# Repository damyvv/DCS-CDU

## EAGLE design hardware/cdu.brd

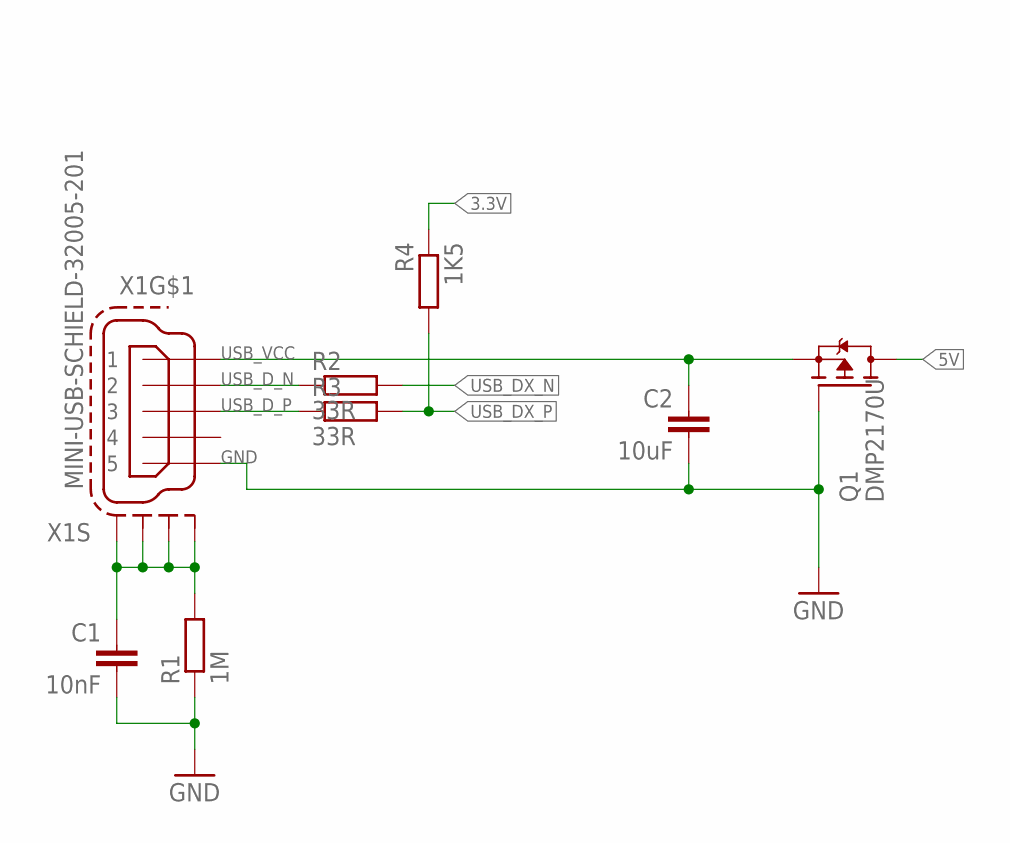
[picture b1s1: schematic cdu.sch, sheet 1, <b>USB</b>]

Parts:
C1: 10nF; C0603
C2: 10uF; C0805K
Q1: DMP2170U; SOT23
R1: 1M; R0603
R2, R3: 33R; R0603
R4: 1K5; R0603
X1: MINI-USB-SCHIELD-32005-201; 32005-201

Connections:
3.3V: R4.1; also elsewhere on the board
5V: Q1.3 (D); also elsewhere on the board
GND: C1.2, C2.2, Q1.1 (G), R1.1, X1.5; also elsewhere on the board
unnamed: C1.1, R1.2, X1.M1 (S1), X1.M2 (S2), X1.M3 (S3), X1.M4 (S4)
USB_DX_N: R2.2; also elsewhere on the board
USB_DX_P: R3.2, R4.2; also elsewhere on the board
USB_D_N: R2.1, X1.2
USB_D_P: R3.1, X1.3
USB_VCC: C2.1, Q1.2 (S), X1.1

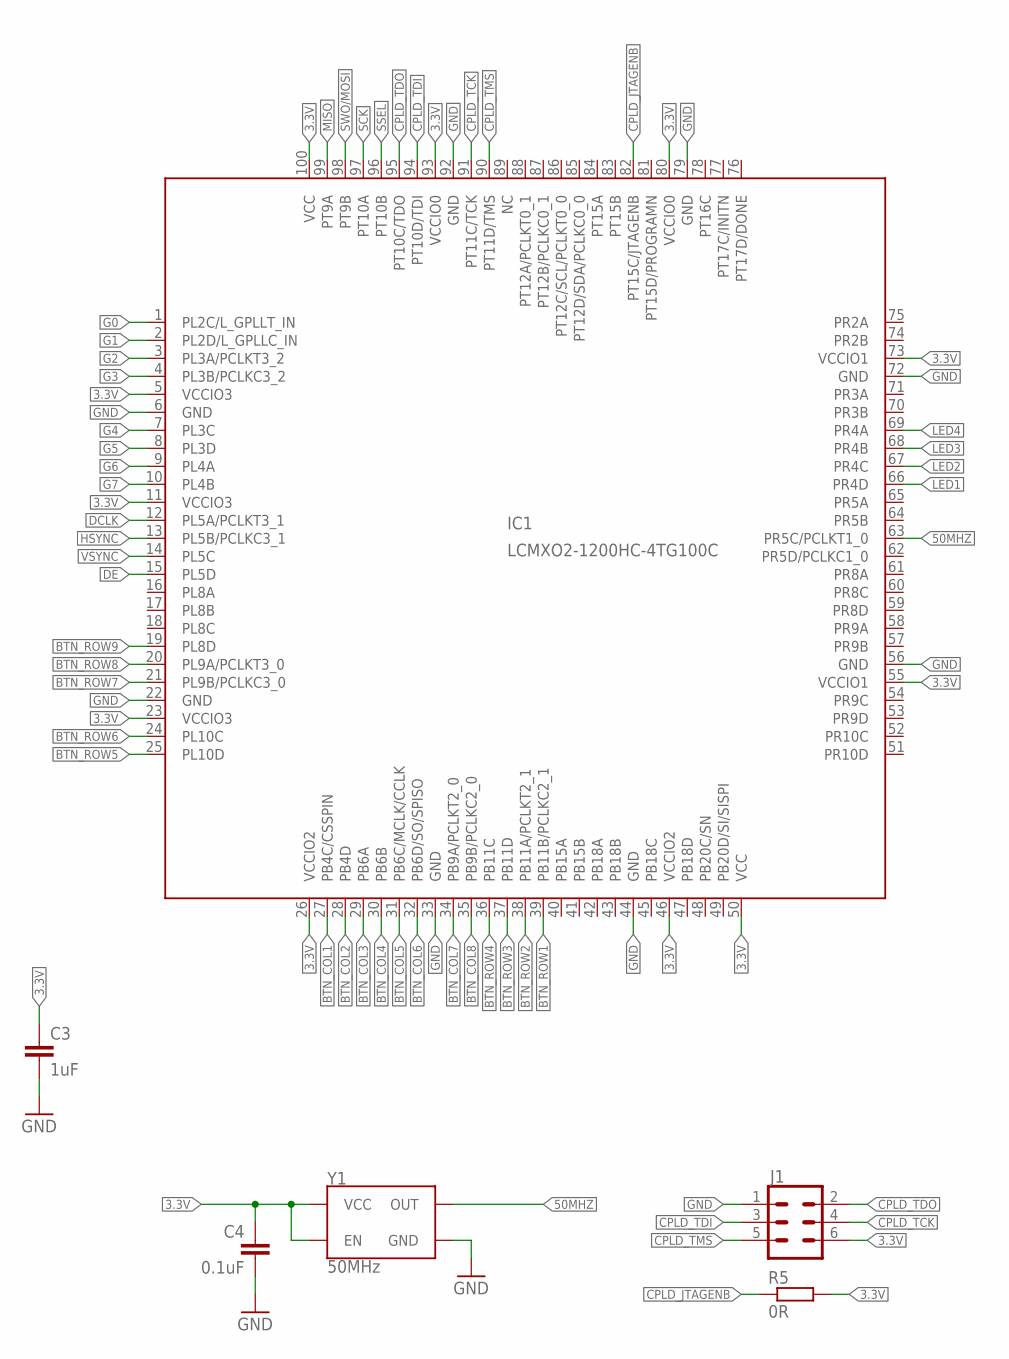
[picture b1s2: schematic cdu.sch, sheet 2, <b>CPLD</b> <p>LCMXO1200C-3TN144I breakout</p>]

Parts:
C3: 1uF; C0603
C4: 0.1uF; C0603
IC1: LCMXO2-1200HC-4TG100C; TQFP100
J1: CONN_03X2FEMALE_SMD; 2X3_SMD
R5: 0R; R0603
Y1: 50MHz; CFPS-73

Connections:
3.3V: C3.1, C4.1, IC1.5 (VCCIO3), IC1.11 (VCCIO3), IC1.23 (VCCIO3), IC1.26 (VCCIO2), IC1.46 (VCCIO2), IC1.50 (VCC), IC1.55 (VCCIO1), IC1.73 (VCCIO1), IC1.80 (VCCIO0), IC1.93 (VCCIO0), IC1.100 (VCC), J1.6, R5.2, Y1.1 (EN), Y1.4 (VCC); also elsewhere on the board
50MHZ: IC1.63 (PR5C/PCLKT1_0), Y1.3 (OUT)
BTN_COL1: IC1.27 (PB4C/CSSPIN); also elsewhere on the board
BTN_COL2: IC1.28 (PB4D); also elsewhere on the board
BTN_COL3: IC1.29 (PB6A); also elsewhere on the board
BTN_COL4: IC1.30 (PB6B); also elsewhere on the board
BTN_COL5: IC1.31 (PB6C/MCLK/CCLK); also elsewhere on the board
BTN_COL6: IC1.32 (PB6D/SO/SPISO); also elsewhere on the board
BTN_COL7: IC1.34 (PB9A/PCLKT2_0); also elsewhere on the board
BTN_COL8: IC1.35 (PB9B/PCLKC2_0); also elsewhere on the board
BTN_ROW1: IC1.39 (PB11B/PCLKC2_1); also elsewhere on the board
BTN_ROW2: IC1.38 (PB11A/PCLKT2_1); also elsewhere on the board
BTN_ROW3: IC1.37 (PB11D); also elsewhere on the board
BTN_ROW4: IC1.36 (PB11C); also elsewhere on the board
BTN_ROW5: IC1.25 (PL10D); also elsewhere on the board
BTN_ROW6: IC1.24 (PL10C); also elsewhere on the board
BTN_ROW7: IC1.21 (PL9B/PCLKC3_0); also elsewhere on the board
BTN_ROW8: IC1.20 (PL9A/PCLKT3_0); also elsewhere on the board
BTN_ROW9: IC1.19 (PL8D); also elsewhere on the board
CPLD_JTAGENB: IC1.82 (PT15C/JTAGENB), R5.1
CPLD_TCK: IC1.91 (PT11C/TCK), J1.4
CPLD_TDI: IC1.94 (PT10D/TDI), J1.3
CPLD_TDO: IC1.95 (PT10C/TDO), J1.2
CPLD_TMS: IC1.90 (PT11D/TMS), J1.5
DCLK: IC1.12 (PL5A/PCLKT3_1); also elsewhere on the board
DE: IC1.15 (PL5D); also elsewhere on the board
G0: IC1.1 (PL2C/L_GPLLT_IN); also elsewhere on the board
G1: IC1.2 (PL2D/L_GPLLC_IN); also elsewhere on the board
G2: IC1.3 (PL3A/PCLKT3_2); also elsewhere on the board
G3: IC1.4 (PL3B/PCLKC3_2); also elsewhere on the board
G4: IC1.7 (PL3C); also elsewhere on the board
G5: IC1.8 (PL3D); also elsewhere on the board
G6: IC1.9 (PL4A); also elsewhere on the board
G7: IC1.10 (PL4B); also elsewhere on the board
GND: C3.2, C4.2, IC1.6 (GND), IC1.22 (GND), IC1.33 (GND), IC1.44 (GND), IC1.56 (GND), IC1.72 (GND), IC1.79 (GND), IC1.92 (GND), J1.1, Y1.2 (GND); also elsewhere on the board
HSYNC: IC1.13 (PL5B/PCLKC3_1); also elsewhere on the board
LED1: IC1.66 (PR4D); also elsewhere on the board
LED2: IC1.67 (PR4C); also elsewhere on the board
LED3: IC1.68 (PR4B); also elsewhere on the board
LED4: IC1.69 (PR4A); also elsewhere on the board
MISO: IC1.99 (PT9A); also elsewhere on the board
SCK: IC1.97 (PT10A); also elsewhere on the board
SSEL: IC1.96 (PT10B); also elsewhere on the board
SWO/MOSI: IC1.98 (PT9B); also elsewhere on the board
VSYNC: IC1.14 (PL5C); also elsewhere on the board

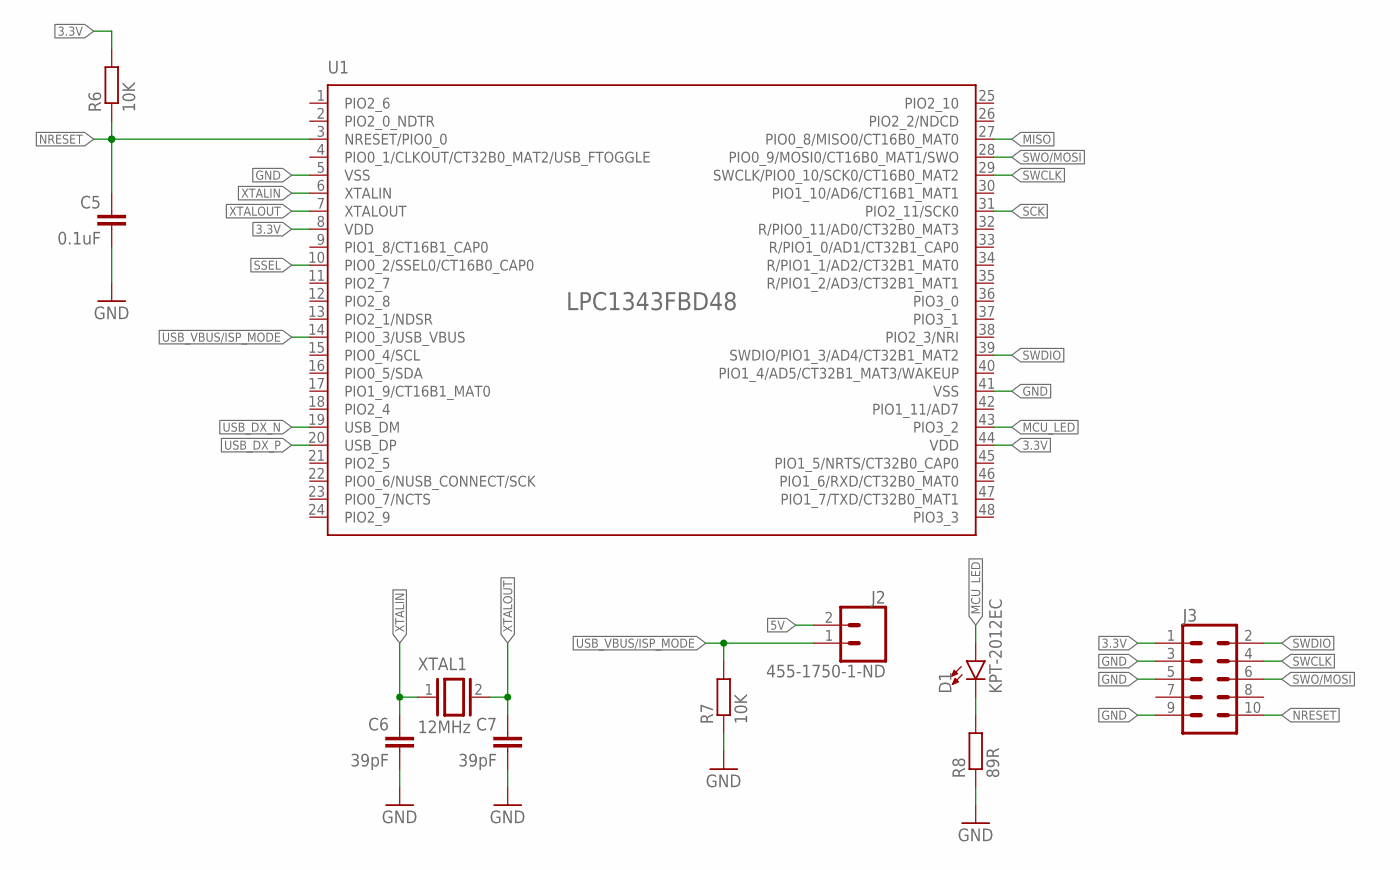
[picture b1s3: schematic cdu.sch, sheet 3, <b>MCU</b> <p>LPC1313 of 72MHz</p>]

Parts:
C5: 0.1uF; C0603
C6, C7: 39pF; C0603
D1: KPT-2012EC
J2: 455-1750-1-ND; 1X02_SMD
J3: CONN_05X2SMD_12.7; 2X5_SMD_1.27MM
R6, R7: 10K; R0603
R8: 89R; R0603
U1: LPC1343FBD48; LQFP-48
XTAL1: 12MHz; CAA-12.000-18-3050-X

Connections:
3.3V: J3.1, R6.2, U1.8 (VDD), U1.44 (VDD); also elsewhere on the board
5V: J2.2; also elsewhere on the board
GND: C5.2, C6.2, C7.2, J3.3, J3.5, J3.9, R7.1, R8.1, U1.5 (VSS), U1.41 (VSS); also elsewhere on the board
MCU_LED: D1.A, U1.43 (PIO3_2)
MISO: U1.27 (PIO0_8/MISO0/CT16B0_MAT0); also elsewhere on the board
unnamed: D1.C, R8.2
NRESET: C5.1, J3.10, R6.1, U1.3 (NRESET/PIO0_0)
SCK: U1.31 (PIO2_11/SCK0); also elsewhere on the board
SSEL: U1.10 (PIO0_2/SSEL0/CT16B0_CAP0); also elsewhere on the board
SWCLK: J3.4, U1.29 (SWCLK/PIO0_10/SCK0/CT16B0_MAT2)
SWDIO: J3.2, U1.39 (SWDIO/PIO1_3/AD4/CT32B1_MAT2)
SWO/MOSI: J3.6, U1.28 (PIO0_9/MOSI0/CT16B0_MAT1/SWO); also elsewhere on the board
USB_DX_N: U1.19 (USB_DM); also elsewhere on the board
USB_DX_P: U1.20 (USB_DP); also elsewhere on the board
USB_VBUS/ISP_MODE: J2.1, R7.2, U1.14 (PIO0_3/USB_VBUS)
XTALIN: C6.1, U1.6 (XTALIN), XTAL1.1
XTALOUT: C7.1, U1.7 (XTALOUT), XTAL1.2

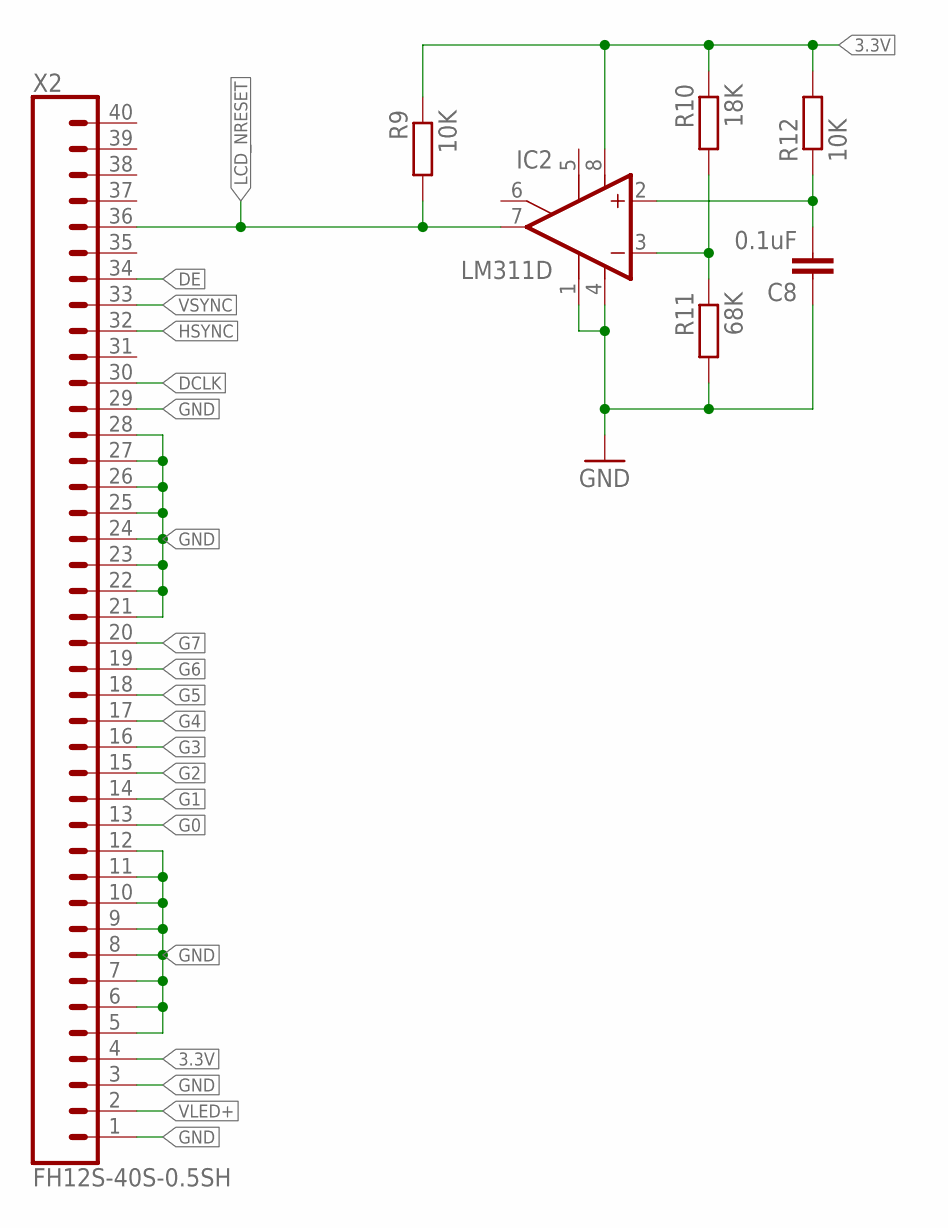
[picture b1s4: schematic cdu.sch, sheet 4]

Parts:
C8: 0.1uF; C0603
IC2: LM311D; SO08
R9, R12: 10K; R0603
R10: 18K; R0603
R11: 68K; R0603
X2: FH12S-40S-0.5SH

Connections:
3.3V: IC2.8 (V+), R9.1, R10.1, R12.2, X2.4; also elsewhere on the board
DCLK: X2.30; also elsewhere on the board
DE: X2.34; also elsewhere on the board
G0: X2.13; also elsewhere on the board
G1: X2.14; also elsewhere on the board
G2: X2.15; also elsewhere on the board
G3: X2.16; also elsewhere on the board
G4: X2.17; also elsewhere on the board
G5: X2.18; also elsewhere on the board
G6: X2.19; also elsewhere on the board
G7: X2.20; also elsewhere on the board
GND: C8.1, IC2.1 (GND), IC2.4 (V-), R11.2, X2.1, X2.3, X2.5, X2.6, X2.7, X2.8, X2.9, X2.10, X2.11, X2.12, X2.21, X2.22, X2.23, X2.24, X2.25, X2.26, X2.27, X2.28, X2.29; also elsewhere on the board
HSYNC: X2.32; also elsewhere on the board
LCD_NRESET: IC2.7 (OUT), R9.2, X2.36
unnamed: C8.2, IC2.2 (+IN), R12.1
unnamed: IC2.3 (-IN), R10.2, R11.1
VLED+: X2.2; also elsewhere on the board
VSYNC: X2.33; also elsewhere on the board

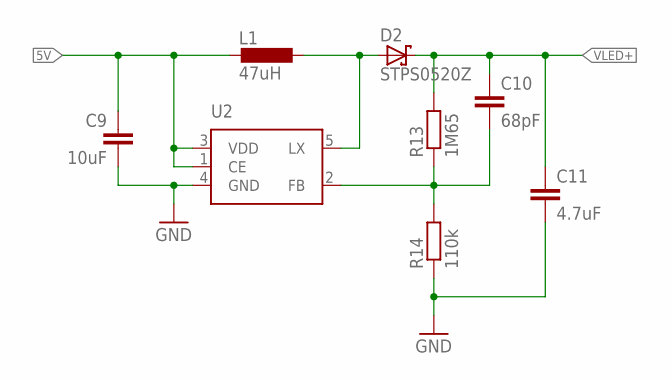
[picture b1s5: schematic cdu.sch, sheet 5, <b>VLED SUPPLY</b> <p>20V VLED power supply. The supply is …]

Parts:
C9: 10uF; C0805K
C10: 68pF; C0603
C11: 4.7uF; C0603
D2: STPS0520Z; SOD123
L1: 47uH; TYS4018470M-10
R13: 1M65; R0603
R14: 110k; R0603
U2: NCP1406; TSOP-5

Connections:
5V: C9.1, L1.2, U2.1 (CE), U2.3 (VDD); also elsewhere on the board
GND: C9.2, C11.2, R14.1, U2.4 (GND); also elsewhere on the board
unnamed: D2.A, L1.1, U2.5 (LX)
unnamed: C10.2, R13.1, R14.2, U2.2 (FB)
VLED+: C10.1, C11.1, D2.C, R13.2; also elsewhere on the board

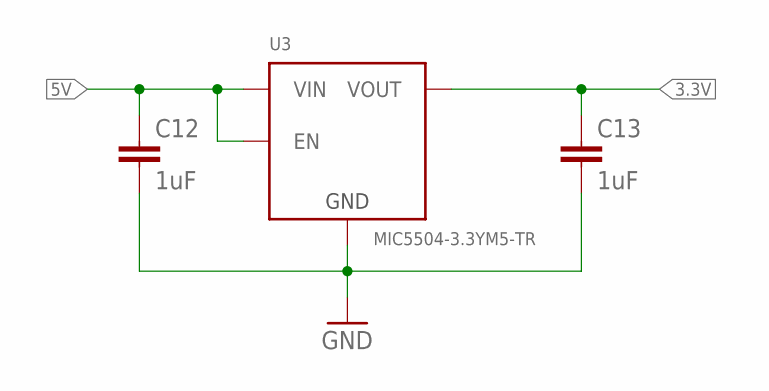
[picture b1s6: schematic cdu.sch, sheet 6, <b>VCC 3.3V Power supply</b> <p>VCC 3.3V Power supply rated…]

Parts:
C12, C13: 1uF; C0603
U3: MIC5504-3.3YM5-TR; SOT23-5

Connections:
3.3V: C13.1, U3.5 (VOUT); also elsewhere on the board
5V: C12.1, U3.1 (VIN), U3.3 (EN); also elsewhere on the board
GND: C12.2, C13.2, U3.2 (GND); also elsewhere on the board

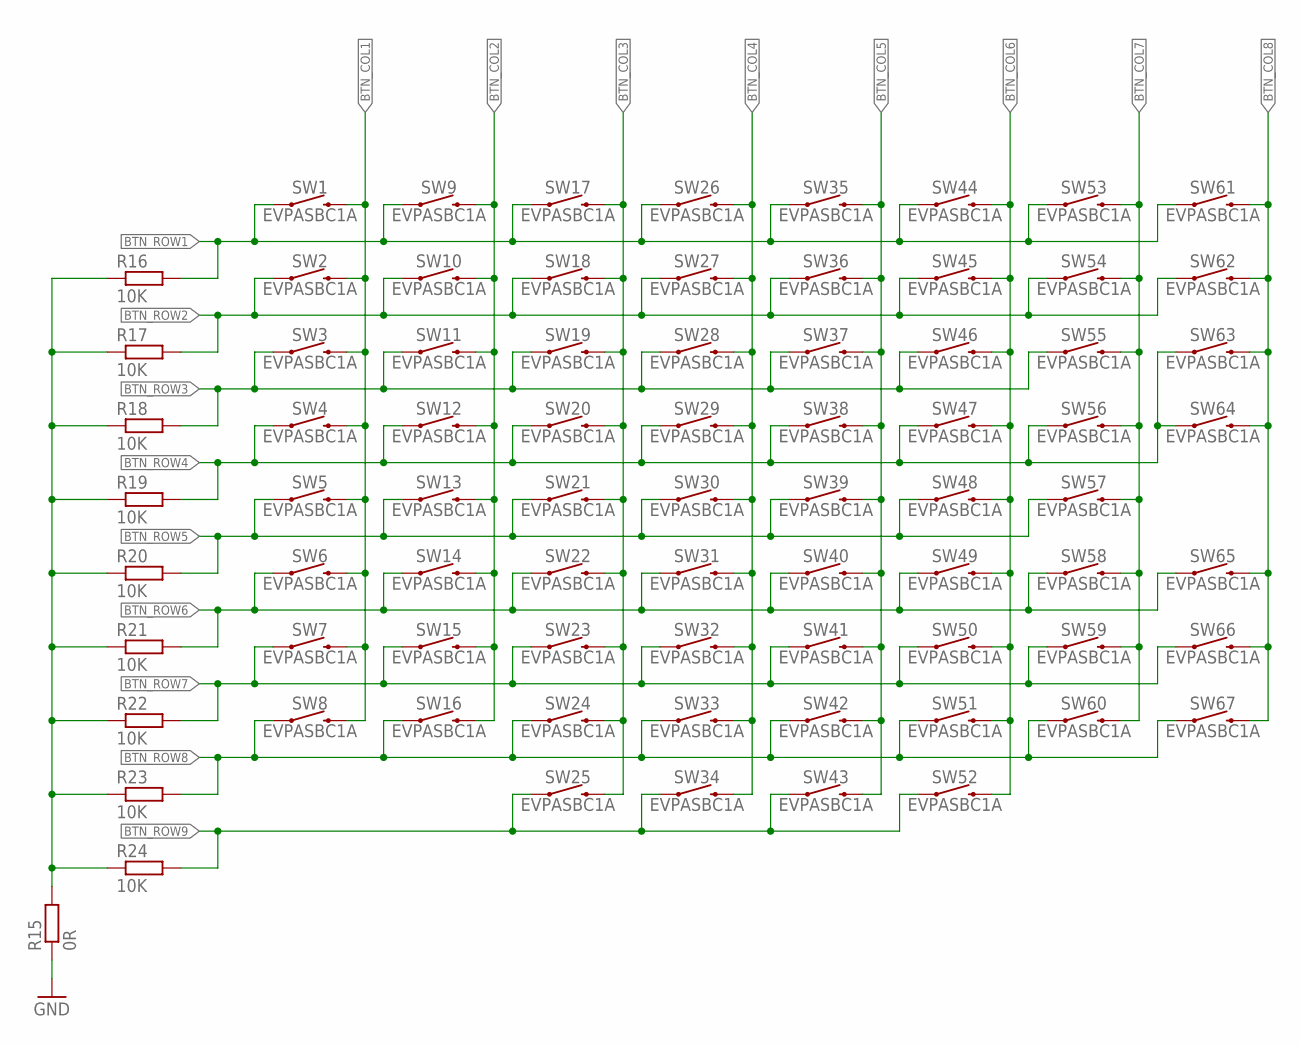
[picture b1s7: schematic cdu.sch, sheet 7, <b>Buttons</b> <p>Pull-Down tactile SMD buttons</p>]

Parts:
R15: 0R; R0603
R16, R17, R18, R19, R20, R21, R22, R23, R24: 10K; R0603
SW1, SW2, SW3, SW4, SW5, SW6, SW7, SW8, SW9, SW10, SW11, SW12, SW13, SW14, SW15, SW16, SW17, SW18, SW19, SW20, SW21, SW22, SW23, SW24, SW25, SW26, SW27, SW28, SW29, SW30, SW31, SW32, SW33, SW34, SW35, SW36, SW37, SW38, SW39, SW40, SW41, SW42, SW43, SW44, SW45, SW46, SW47, SW48, SW49, SW50, SW51, SW52, SW53, SW54, SW55, SW56, SW57, SW58, SW59, SW60, SW61, SW62, SW63, SW64, SW65, SW66, SW67: EVPASBC1A

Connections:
BTN_COL1: SW1.P$2 (2), SW2.P$2 (2), SW3.P$2 (2), SW4.P$2 (2), SW5.P$2 (2), SW6.P$2 (2), SW7.P$2 (2), SW8.P$2 (2); also elsewhere on the board
BTN_COL2: SW9.P$2 (2), SW10.P$2 (2), SW11.P$2 (2), SW12.P$2 (2), SW13.P$2 (2), SW14.P$2 (2), SW15.P$2 (2), SW16.P$2 (2); also elsewhere on the board
BTN_COL3: SW17.P$2 (2), SW18.P$2 (2), SW19.P$2 (2), SW20.P$2 (2), SW21.P$2 (2), SW22.P$2 (2), SW23.P$2 (2), SW24.P$2 (2), SW25.P$2 (2); also elsewhere on the board
BTN_COL4: SW26.P$2 (2), SW27.P$2 (2), SW28.P$2 (2), SW29.P$2 (2), SW30.P$2 (2), SW31.P$2 (2), SW32.P$2 (2), SW33.P$2 (2), SW34.P$2 (2); also elsewhere on the board
BTN_COL5: SW35.P$2 (2), SW36.P$2 (2), SW37.P$2 (2), SW38.P$2 (2), SW39.P$2 (2), SW40.P$2 (2), SW41.P$2 (2), SW42.P$2 (2), SW43.P$2 (2); also elsewhere on the board
BTN_COL6: SW44.P$2 (2), SW45.P$2 (2), SW46.P$2 (2), SW47.P$2 (2), SW48.P$2 (2), SW49.P$2 (2), SW50.P$2 (2), SW51.P$2 (2), SW52.P$2 (2); also elsewhere on the board
BTN_COL7: SW53.P$2 (2), SW54.P$2 (2), SW55.P$2 (2), SW56.P$2 (2), SW57.P$2 (2), SW58.P$2 (2), SW59.P$2 (2), SW60.P$2 (2); also elsewhere on the board
BTN_COL8: SW61.P$2 (2), SW62.P$2 (2), SW63.P$2 (2), SW64.P$2 (2), SW65.P$2 (2), SW66.P$2 (2), SW67.P$2 (2); also elsewhere on the board
BTN_ROW1: R16.2, SW1.P$1 (1), SW9.P$1 (1), SW17.P$1 (1), SW26.P$1 (1), SW35.P$1 (1), SW44.P$1 (1), SW53.P$1 (1), SW61.P$1 (1); also elsewhere on the board
BTN_ROW2: R17.2, SW2.P$1 (1), SW10.P$1 (1), SW18.P$1 (1), SW27.P$1 (1), SW36.P$1 (1), SW45.P$1 (1), SW54.P$1 (1), SW62.P$1 (1); also elsewhere on the board
BTN_ROW3: R18.2, SW3.P$1 (1), SW11.P$1 (1), SW19.P$1 (1), SW28.P$1 (1), SW37.P$1 (1), SW46.P$1 (1), SW55.P$1 (1); also elsewhere on the board
BTN_ROW4: R19.2, SW4.P$1 (1), SW12.P$1 (1), SW20.P$1 (1), SW29.P$1 (1), SW38.P$1 (1), SW47.P$1 (1), SW56.P$1 (1), SW63.P$1 (1), SW64.P$1 (1); also elsewhere on the board
BTN_ROW5: R20.2, SW5.P$1 (1), SW13.P$1 (1), SW21.P$1 (1), SW30.P$1 (1), SW39.P$1 (1), SW48.P$1 (1), SW57.P$1 (1); also elsewhere on the board
BTN_ROW6: R21.2, SW6.P$1 (1), SW14.P$1 (1), SW22.P$1 (1), SW31.P$1 (1), SW40.P$1 (1), SW49.P$1 (1), SW58.P$1 (1), SW65.P$1 (1); also elsewhere on the board
BTN_ROW7: R22.2, SW7.P$1 (1), SW15.P$1 (1), SW23.P$1 (1), SW32.P$1 (1), SW41.P$1 (1), SW50.P$1 (1), SW59.P$1 (1), SW66.P$1 (1); also elsewhere on the board
BTN_ROW8: R23.2, SW8.P$1 (1), SW16.P$1 (1), SW24.P$1 (1), SW33.P$1 (1), SW42.P$1 (1), SW51.P$1 (1), SW60.P$1 (1), SW67.P$1 (1); also elsewhere on the board
BTN_ROW9: R24.2, SW25.P$1 (1), SW34.P$1 (1), SW43.P$1 (1), SW52.P$1 (1); also elsewhere on the board
GND: R15.1; also elsewhere on the board
unnamed: R15.2, R16.1, R17.1, R18.1, R19.1, R20.1, R21.1, R22.1, R23.1, R24.1

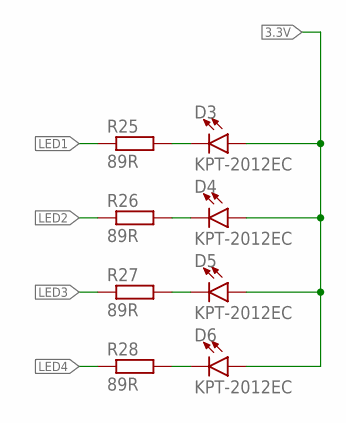
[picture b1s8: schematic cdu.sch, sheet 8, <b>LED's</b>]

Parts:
D3, D4, D5, D6: KPT-2012EC
R25, R26, R27, R28: 89R; R0603

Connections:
3.3V: D3.A, D4.A, D5.A, D6.A; also elsewhere on the board
LED1: R25.1; also elsewhere on the board
LED2: R26.1; also elsewhere on the board
LED3: R27.1; also elsewhere on the board
LED4: R28.1; also elsewhere on the board
unnamed: D4.C, R26.2
unnamed: D5.C, R27.2
unnamed: D6.C, R28.2
unnamed: D3.C, R25.2

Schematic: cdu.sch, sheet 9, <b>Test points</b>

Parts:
TP1, TP2, TP3, TP4: TEST-POINT3X4; PAD.03X.04

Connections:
3.3V: TP3.P$1; also elsewhere on the board
5V: TP2.P$1; also elsewhere on the board
GND: TP1.P$1; also elsewhere on the board
VLED+: TP4.P$1; also elsewhere on the board

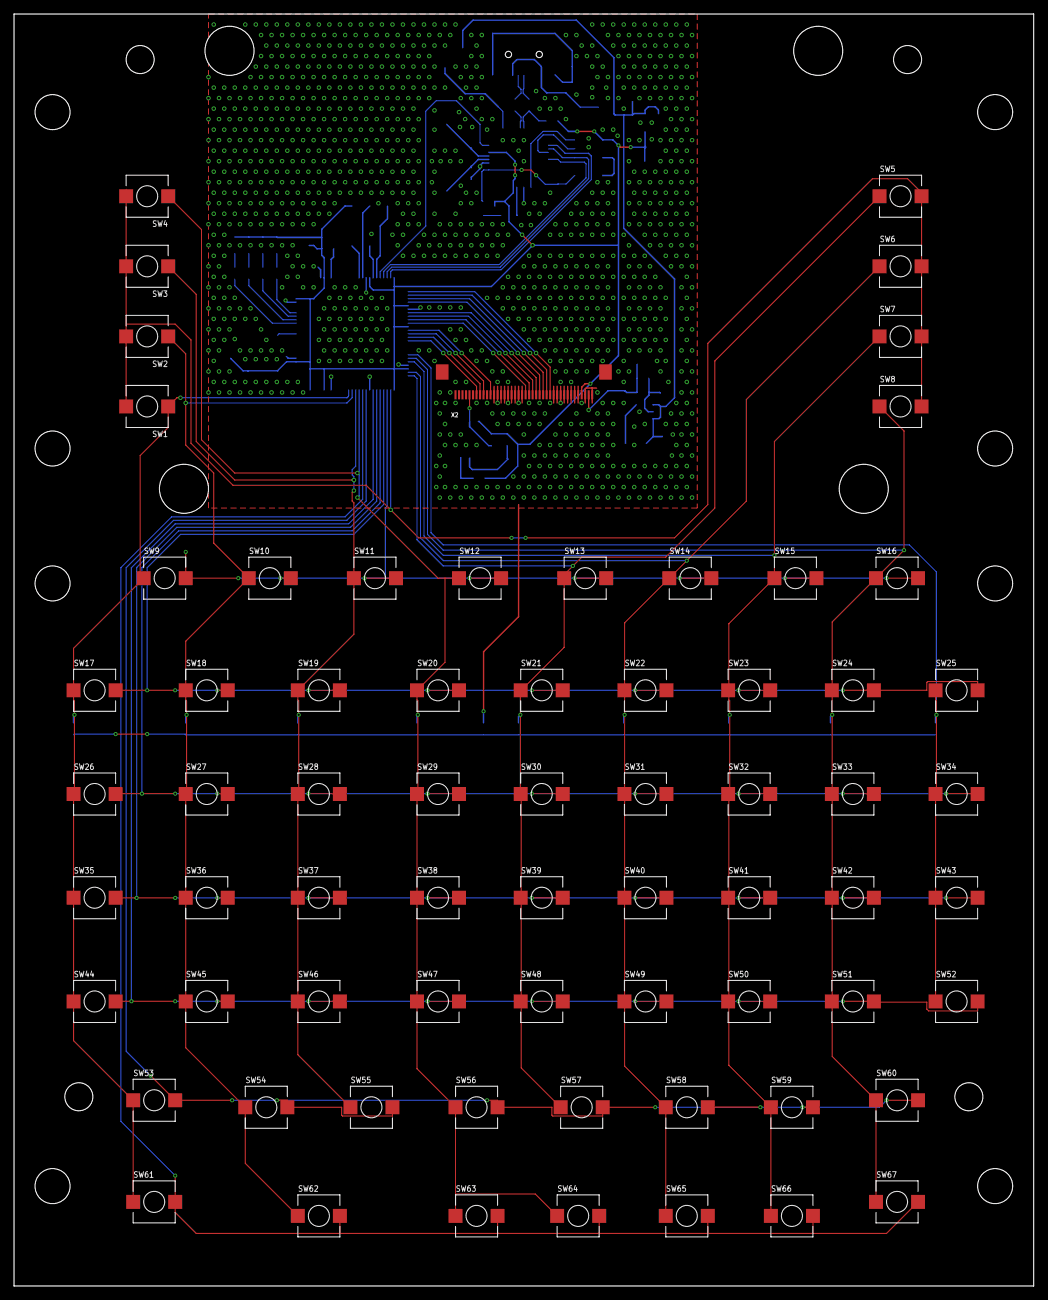
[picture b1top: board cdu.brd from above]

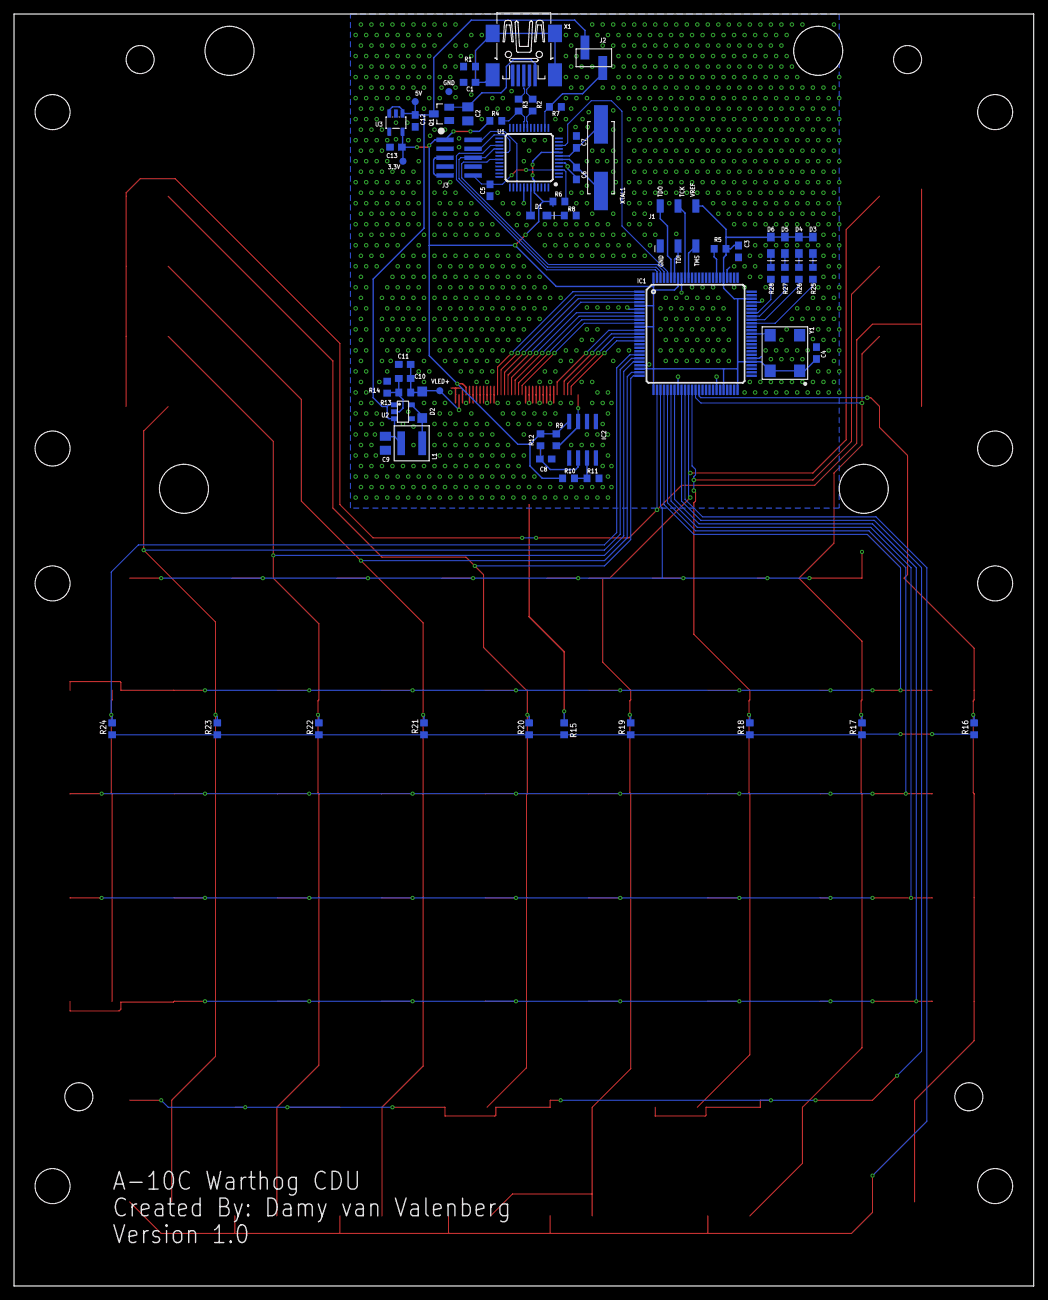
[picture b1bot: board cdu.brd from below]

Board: 2 copper layers, 145.5 x 181.5 mm, 132 parts (64 on the bottom side), 71 nets.

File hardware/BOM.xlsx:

Qty | Value | Farnell ON | Device | Package | Parts | Description
1 | 10nF | 9406182 | C-EUC0603 | C0603 | C1 | CAPACITOR, European symbol
1 | 68pF | 2496910 | C-EUC0603 | C0603 | C10 | CAPACITOR, European symbol
1 | 4.7uF | 2524874 | C-EUC0603 | C0603 | C11 | CAPACITOR, European symbol
2 | 10uF | 1735530 | C-EUC0805K | C0805K | C2, C9 | CAPACITOR, European symbol
3 | 1uF | 2522398 | C-EUC0603 | C0603 | C3, C12, C13 | CAPACITOR, European symbol
3 | 0.1uF | 1828918 | C-EUC0603 | C0603 | C4, C5, C8 | CAPACITOR, European symbol
2 | 39pF | 2496903 | C-EUC0603 | C0603 | C6, C7 | CAPACITOR, European symbol
5 | KPT-2012EC | 2099236 | KPT-2012EC | KPT-2012EC | D1, D3, D4, D5, D6
1 | STPS0520Z | 1467545 | STPS0520Z | SOD123 | D2
1 | LCMXO2-1200HC-4TG100C | 2252976 | LCMXO2-1200HC-4TG100C | TQFP100 | IC1 | edit this description
1 | LM311D | 2293183 | LM311D | SO08 | IC2 | COMPARATOR
1 |  | 2505014 | CONN_03X2FEMALE_SMD | 2X3_SMD | J1 | Multi connection point. Often used as Generic Header-pin footprint for 0.1 inch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
1 | 455-1750-1-ND | 2505008 | CONN_02SMD | 1X02_SMD | J2 | Multi connection point. Often used as Generic Header-pin footprint for 0.1 inch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
1 |  | 2529589 | CONN_05X2SMD_12.7 | 2X5_SMD_1.27MM | J3 | Multi connection point. Often used as Generic Header-pin footprint for 0.1 inch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
1 | 47uH | 2292522 | TYS4018470M-10 | TYS4018470M-10 | L1
1 | DMP2170U | 2709531 | DMP2170U | SOT23 | Q1
1 | 1M | 2074171 | R-EU_R0603 | R0603 | R1 | RESISTOR, European symbol
1 | 18K | 2447269 | R-EU_R0603 | R0603 | R10 | RESISTOR, European symbol
1 | 68K | 2447420 | R-EU_R0603 | R0603 | R11 | RESISTOR, European symbol
1 | 1M65 | 2138632 | R-EU_R0603 | R0603 | R13 | RESISTOR, European symbol
1 | 110k | 2447234 | R-EU_R0603 | R0603 | R14 | RESISTOR, European symbol
2 | 33R | 2073471 | R-EU_R0603 | R0603 | R2, R3 | RESISTOR, European symbol
1 | 1K5 | 2073395 | R-EU_R0603 | R0603 | R4 | RESISTOR, European symbol
2 | 0R | 2447743 | R-EU_R0603 | R0603 | R5, R15 | RESISTOR, European symbol
13 | 10K | 2447230 | R-EU_R0603 | R0603 | R6, R7, R9, R12, R16, R17, R18, R19, R20, R21, R22, R23, R24 | RESISTOR, European symbol
5 | 89R | 2141271 | R-EU_R0603 | R0603 | R8, R25, R26, R27, R28 | RESISTOR, European symbol
67 | EVPASBC1A | 2425611 | EVPASBC1A | EVPASBC1A | SW1, SW2, SW3, SW4, SW5, SW6, SW7, SW8, SW9, SW10, SW11, SW12, SW13, SW14, SW15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
1 | LPC1343FBD48 | 2072195 | LPC1343FBD48 | LQFP-48 | U1
1 | NCP1406 | 2534277 | NCP1406 | TSOP-5 | U2
1 | MIC5504-3.3YM5-TR | 2510377 | MIC5504-3.3YM5-TR | SOT23-5 | U3
1 | MINI-USB-SCHIELD-32005-201 | 1243250 | MINI-USB-SCHIELD-32005-201 | 32005-201 | X1 | MINI USB-B Conector
1 | FH12S-40S-0.5SH | 2135964 | FH12S-40S-0.5SH | FH12S-40S-0.5SH | X2
1 | 12MHz | 1538768 | CRYSTAL | CAA-12.000-18-3050-X | XTAL1
1 | 50MHz | 2449411 | LFSPXO019987 | CFPS-73 | Y1

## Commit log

2019-01-31 Added LPC firmware
2019-01-31 Added CPLD firmware
2019-01-31 Added the hardware schematic and gerber files
2019-01-31 Added PC driver
2019-01-31 Create LICENSE

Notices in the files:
parts and their libraries:
SparkFun-Connectors: Licensing: Creative Commons ShareAlike 4.0 International - https://creativecommons.org/licenses/by-sa/4.0
